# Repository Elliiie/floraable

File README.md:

# floraable
Plant controlling and monitoring system for busy people

Документация: https://docs.google.com/document/d/1ffq8gmJn7NOZOaIAXpCDWpJQ3-BypjiNOwnWwaLyr4o/edit?usp=sharing

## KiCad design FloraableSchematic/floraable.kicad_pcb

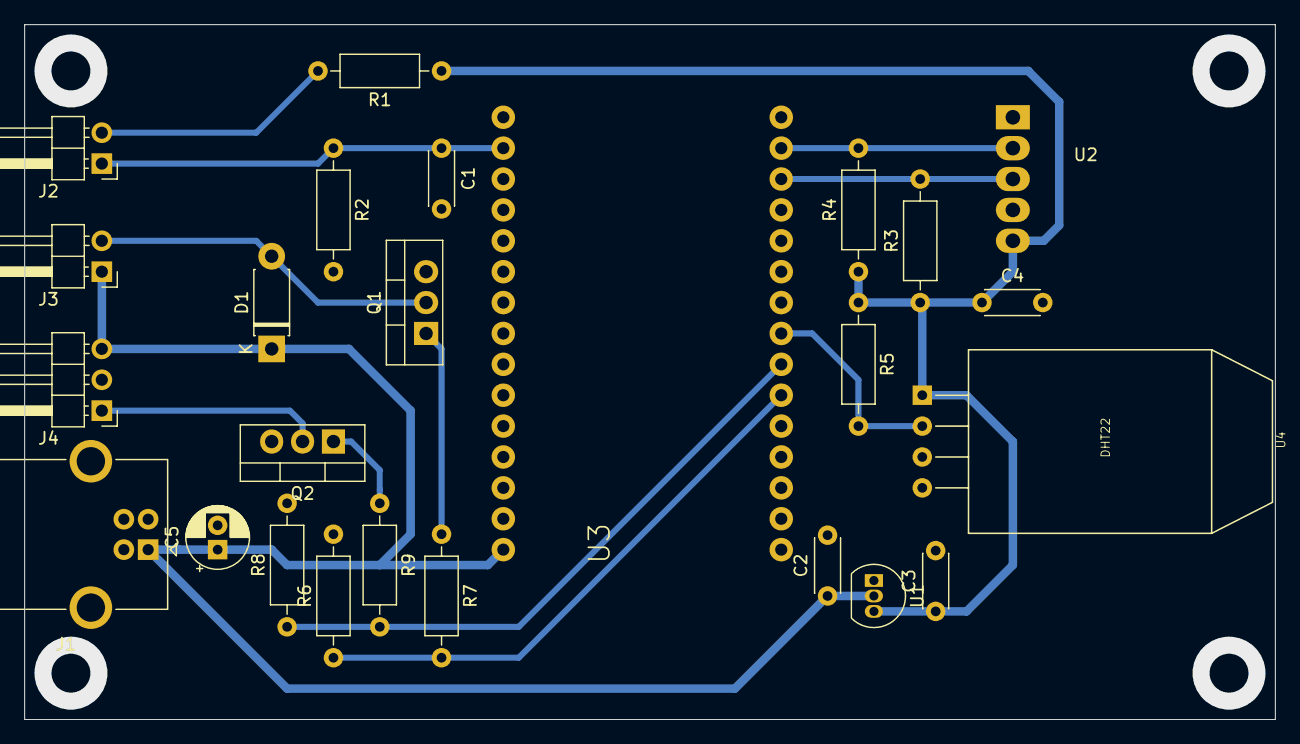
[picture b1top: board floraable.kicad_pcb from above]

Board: 2 copper layers, 102.9 x 57.2 mm, 25 parts (0 on the bottom side), 14 nets.

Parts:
C1, C4: 100n; C_Disc_D4.3mm_W1.9mm_P5.00mm
C2, C3: 1u; C_Disc_D4.3mm_W1.9mm_P5.00mm
C5: 100u; CP_Radial_D5.0mm_P2.00mm
D1: D1; D_DO-41_SOD81_P7.62mm_Horizontal
J1: USB_B; USB_B_OST_USB-B1HSxx_Horizontal
J2: soil moisture sensor; PinHeader_1x02_P2.54mm_Horizontal
J3: water pump; PinHeader_1x02_P2.54mm_Horizontal
J4: LED strip; PinHeader_1x03_P2.54mm_Horizontal
Q1, Q2: IRL1404Z; TO-220-3_Vertical
R1: 22k; R_Axial_DIN0207_L6.3mm_D2.5mm_P10.16mm_Horizontal
R2: 10k; R_Axial_DIN0207_L6.3mm_D2.5mm_P10.16mm_Horizontal
R3, R4, R5: 4.7k; R_Axial_DIN0207_L6.3mm_D2.5mm_P10.16mm_Horizontal
R6, R8: 15k; R_Axial_DIN0207_L6.3mm_D2.5mm_P10.16mm_Horizontal
R7, R9: 150R; R_Axial_DIN0207_L6.3mm_D2.5mm_P10.16mm_Horizontal
U1: MCP1702-3302E/TO; TO-92_Inline
U2: BH1750_module
U3: NodeMCU; newNodeMCU
U4: DHT22; SNR4-2.54-25.0X15.0X7.0MM

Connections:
+3V3: C3.1, C4.1, R1.1, R3.1, R4.1, R5.1, U1.3, U2.5, U4.P$1
+5V: C2.1, C5.1, D1.1, J1.1, J3.1, J4.3, U1.2, U3.VIN
GND: C1.2, C2.2, C3.2, C4.2, C5.2, J1.4, J1.5, Q1.3, Q2.3, R2.2, R6.2, R8.2, U1.1, U2.4, U3.GND@0, U3.GND@1, U3.GND@2, U3.GND@3, U4.P$4
LEDSTRIP: R8.1, R9.2, U3.D6
unnamed: D1.2, J3.2, Q1.2
unnamed: J2.2, R1.2
unnamed: J4.1, Q2.2
unnamed: Q1.1, R7.1
unnamed: Q2.1, R9.1
PUMP: R6.1, R7.2, U3.D7
SCL: R3.2, U2.3, U3.D2
SDA: R4.2, U2.2, U3.D1
SOIL: C1.1, J2.1, R2.1, U3.RSV@0
TEMPERATURE: R5.2, U3.D5, U4.P$2

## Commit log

2019-11-26 authentication done
2019-12-14 user and device relationship done
2020-01-09 added admin panel and devices to profiles
2020-02-10 added schematic folder
2020-02-10 new folder
2020-02-11 nodeMCU code
2020-02-19 check for existing devices
2020-02-20 fixed mqtt subscribers and publishers
2020-02-20 fixed some errors
2020-02-24 added table for humidity values
2020-02-24 separate functions for sending temperature, light and soil moisture measurements
2020-03-04 added autopilot option and some css
2020-03-05 added multiple client handling
2020-03-10 fixed on_message function
2020-03-10 fixed dht function
2020-03-12 added non-blocking delay
2020-03-23 new schematic
